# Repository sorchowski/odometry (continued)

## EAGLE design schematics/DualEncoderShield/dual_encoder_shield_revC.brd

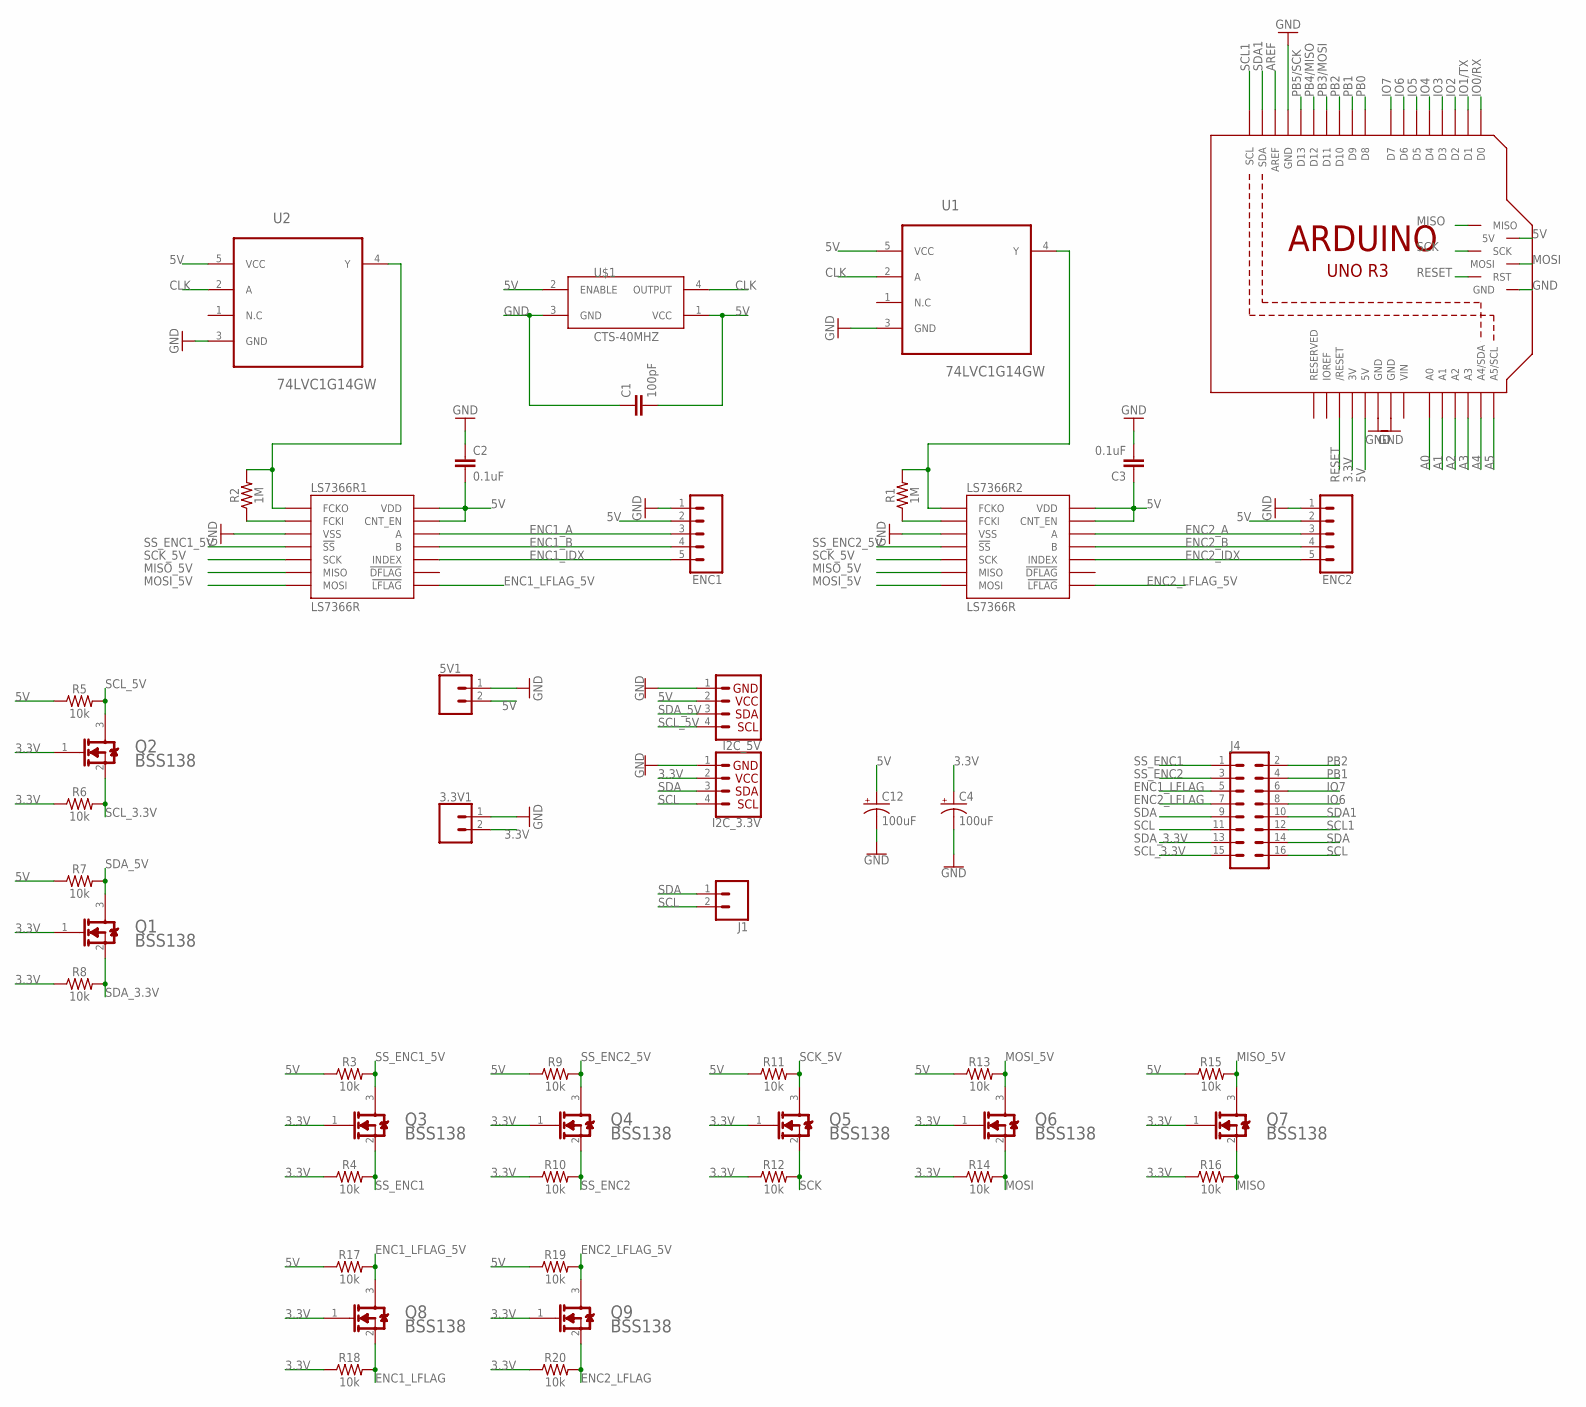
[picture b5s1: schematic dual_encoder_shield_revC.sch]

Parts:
3.3V1, 5V1: CONN_02-JST-2MM-SMT; JST-2-SMD
C1: 100pF; 0603
C2, C3: 0.1uF; 0603
C4, C12: 100uF; PANASONIC_D
ENC1, ENC2: CONN_05; 1X05
I2C_3.3V, I2C_5V: QWIIC_CONNECTORJS-1MM; JST04_1MM_RA
J1: CONN_02; 1X02
J4: CONN_08X2; 2X8
LS7366R1, LS7366R2: LS7366R; SOIC14
M1: ARDUINO_R3_ICSP; ARDUINOR3_ICSP
Q1, Q2, Q3, Q4, Q5, Q6, Q7, Q8, Q9: ON_SEMI_BSS138ON_SEMI_BSS138_0_0; ON_SEMI_BSS138_0
R1, R2: 1M; 0603
R3, R4, R5, R6, R7, R8, R9, R10, R11, R12, R13, R14, R15, R16, R17, R18, R19, R20: 10k; 0603
U1, U2: 74LVC1G14GW; SOT65P210X110-5N
U$1: CTS-40MHZ; SOIC254P1016X440-4N

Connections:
3.3V: 3.3V1.2 (1), C4.+, I2C_3.3V.2, M1.3V, Q1.1 (G), Q2.1 (G), Q3.1 (G), Q4.1 (G), Q5.1 (G), Q6.1 (G), Q7.1 (G), Q8.1 (G), Q9.1 (G), R4.1, R6.1, R8.1, R10.1, R12.1, R14.1, R16.1, R18.1, R20.1
5V: 5V1.2 (1), C1.2, C2.2, C3.1, C12.+, ENC1.2, ENC2.2, I2C_5V.2, LS7366R1.13 (CNT_EN), LS7366R1.14 (VDD), LS7366R2.13 (CNT_EN), LS7366R2.14 (VDD), M1.5V, M1.5V_ICSP (5V), R3.1, R5.1, R7.1, R9.1, R11.1, R13.1, R15.1, R17.1, R19.1, U1.5 (VCC), U2.5 (VCC), U$1.1 (VCC), U$1.2 (ENABLE)
A0: M1.A0
A1: M1.A1
A2: M1.A2
A3: M1.A3
A4: M1.A4 (A4/SDA)
A5: M1.A5 (A5/SCL)
AREF: M1.AREF
CLK: U1.2 (A), U2.2 (A), U$1.4 (OUTPUT)
ENC1_A: ENC1.3, LS7366R1.12 (A)
ENC1_B: ENC1.4, LS7366R1.11 (B)
ENC1_IDX: ENC1.5, LS7366R1.10 (INDEX)
ENC1_LFLAG: J4.5, Q8.2 (S), R18.2
ENC1_LFLAG_5V: LS7366R1.8 (!LFLAG), Q8.3 (D), R17.2
ENC2_A: ENC2.3, LS7366R2.12 (A)
ENC2_B: ENC2.4, LS7366R2.11 (B)
ENC2_IDX: ENC2.5, LS7366R2.10 (INDEX)
ENC2_LFLAG: J4.7, Q9.2 (S), R20.2
ENC2_LFLAG_5V: LS7366R2.8 (!LFLAG), Q9.3 (D), R19.2
GND: 3.3V1.1 (2), 5V1.1 (2), C1.1, C2.1, C3.2, C4.-, C12.-, ENC1.1, ENC2.1, I2C_3.3V.1, I2C_5V.1, LS7366R1.3 (VSS), LS7366R2.3 (VSS), M1.GND, M1.GND@1 (GND), M1.GND@2 (GND), M1.GND@3 (GND), U1.3 (GND), U2.3 (GND), U$1.3 (GND)
IO0/RX: M1.D0
IO1/TX: M1.D1
IO2: M1.D2
IO3: M1.D3
IO4: M1.D4
IO5: M1.D5
IO6: J4.8, M1.D6
IO7: J4.6, M1.D7
MISO: M1.MISO, Q7.2 (S), R16.2
MISO_5V: LS7366R1.6 (MISO), LS7366R2.6 (MISO), Q7.3 (D), R15.2
MOSI: M1.MOSI, Q6.2 (S), R14.2
MOSI_5V: LS7366R1.7 (MOSI), LS7366R2.7 (MOSI), Q6.3 (D), R13.2
unnamed: LS7366R1.2 (FCKI), R2.1
unnamed: LS7366R2.1 (FCKO), R1.2, U1.4 (Y)
unnamed: LS7366R2.2 (FCKI), R1.1
unnamed: LS7366R1.1 (FCKO), R2.2, U2.4 (Y)
PB0: M1.D8
PB1: J4.4, M1.D9
PB2: J4.2, M1.D10
PB3/MOSI: M1.D11
PB4/MISO: M1.D12
PB5/SCK: M1.D13
RESET: M1.RESET (/RESET), M1.RESET_ICSP (RST)
SCK: M1.SCK, Q5.2 (S), R12.2
SCK_5V: LS7366R1.5 (SCK), LS7366R2.5 (SCK), Q5.3 (D), R11.2
SCL: I2C_3.3V.4, J1.2, J4.11, J4.16
SCL1: J4.12, M1.SCL
SCL_3.3V: J4.15, Q2.2 (S), R6.2
SCL_5V: I2C_5V.4, Q2.3 (D), R5.2
SDA: I2C_3.3V.3, J1.1, J4.9, J4.14
SDA1: J4.10, M1.SDA
SDA_3.3V: J4.13, Q1.2 (S), R8.2
SDA_5V: I2C_5V.3, Q1.3 (D), R7.2
SS_ENC1: J4.1, Q3.2 (S), R4.2
SS_ENC1_5V: LS7366R1.4 (!SS), Q3.3 (D), R3.2
SS_ENC2: J4.3, Q4.2 (S), R10.2
SS_ENC2_5V: LS7366R2.4 (!SS), Q4.3 (D), R9.2
VIN: M1.VIN

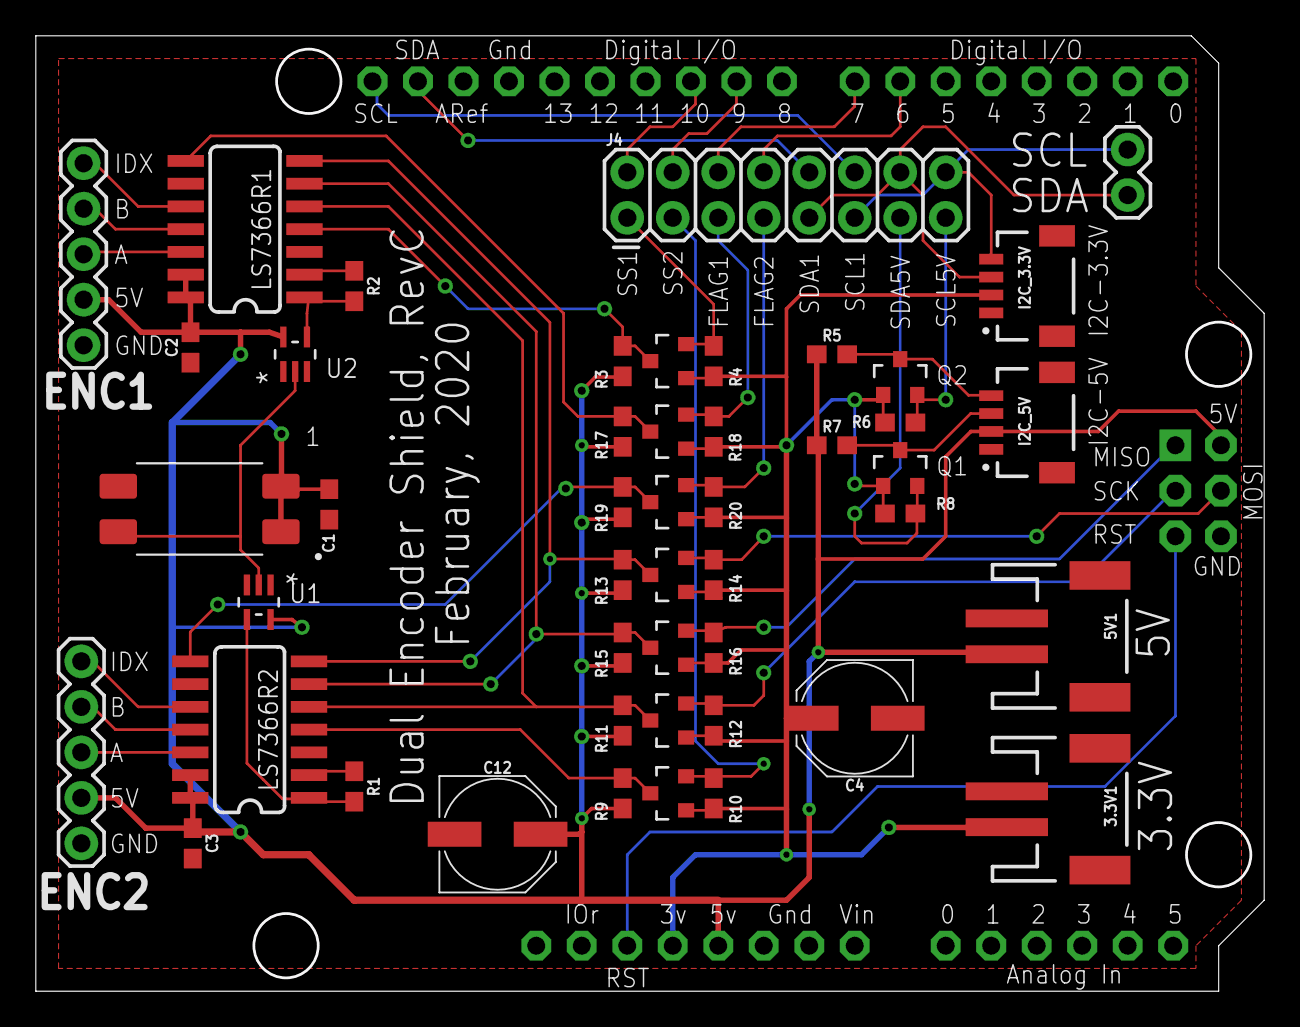
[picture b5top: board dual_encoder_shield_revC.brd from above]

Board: 2 copper layers, 68.4 x 53.2 mm, 48 parts (0 on the bottom side), 41 nets.

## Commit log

2022-10-30 Establish basic directory structure, copy files from other projects
2022-10-30 Add schematic files from eagle project
2022-10-30 move sketches to src
2022-10-30 move ls7366 and velocity to lib
2022-11-09 remove unnecessary schematic versions
2022-12-03 Add i2c support
2023-02-08 Update readme, sketches, and schematics
2023-02-08 fix readme links
2023-02-27 Add TODO
2023-11-25 Add support for wheel radians/s
2023-11-26 Add testing section to readme, rearrange various files
2023-11-26 Add testing image and update readme
2023-12-03 update licensing/copyright
2023-12-03 remoef vscode file
2023-12-03 add 5v shield pic
